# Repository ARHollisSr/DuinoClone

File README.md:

# DuinoClone
Arduino Clone with EEPROM

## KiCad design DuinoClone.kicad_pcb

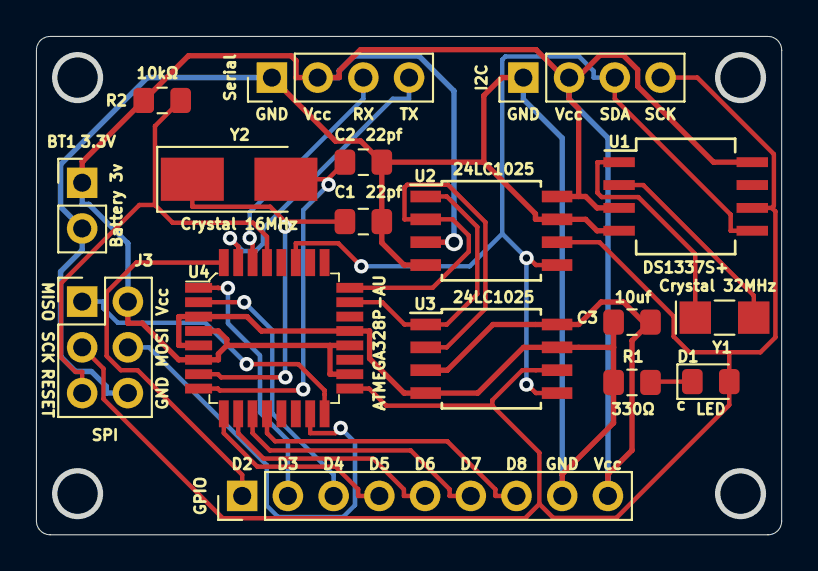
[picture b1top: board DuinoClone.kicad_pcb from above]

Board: 2 copper layers, 41.4 x 27.7 mm, 17 parts (0 on the bottom side), 23 nets.

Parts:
BT1: Battery 3v; PinHeader_1x02_P2.54mm_Vertical
C1, C2: 22pf; C_0805_2012Metric_Pad1.15x1.40mm_HandSolder
C3: 10uf; C_0805_2012Metric_Pad1.15x1.40mm_HandSolder
D1: LED; LED_0805_2012Metric_Pad1.15x1.40mm_HandSolder
GPIO: Digital pins; PinHeader_1x09_P2.54mm_Vertical
I2C: I2C; PinHeader_1x04_P2.54mm_Vertical
J3: SPI; PinHeader_2x03_P2.54mm_Vertical
R1: 330Ω; R_0805_2012Metric_Pad1.15x1.40mm_HandSolder
R2: 10kΩ; R_0805_2012Metric_Pad1.15x1.40mm_HandSolder
Serial: Serial; PinHeader_1x04_P2.54mm_Vertical
U1: DS1337S+; SO-8_5.3x6.2mm_P1.27mm
U2, U3: 24LC1025; SOIJ-8_5.3x5.3mm_P1.27mm
U4: ATMEGA328P-AU; TQFP-32_7x7mm
Y1: Crystal 32MHz; Crystal_SMD_MicroCrystal_CC7V-T1A-2Pin_3.2x1.5mm_HandSolder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
Y2: Crystal 16MHz; Crystal_SMD_5032-2Pin_5.0x3.2mm_HandSoldering

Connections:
/ADDS1: U2.1, U3.1, U4.23
/ADDS2: U2.2, U3.2, U4.24
/D2: GPIO.1, U4.32
/D3: GPIO.2, U4.1
/D4: GPIO.3, U4.2
/D5: GPIO.4, U4.9
/D6: GPIO.5, U4.10
/D7: GPIO.6, U4.11
/D8: GPIO.7, U4.12
/MISO: J3.1, U4.16
/MOSI: J3.4, U4.15
/RESET: J3.5, R2.1, U4.29
/RX: Serial.3, U4.30
/SCK: D1.2, I2C.4, J3.3, U1.6, U2.6, U3.6, U4.17
/SDA: I2C.3, U1.5, U2.5, U3.5, U4.27
/TX: Serial.4, U4.31
/Vcc: BT1.1, C3.1, GPIO.9, I2C.2, J3.2, R2.2, Serial.2, U1.3, U1.8, U2.3, U2.8, U3.3, U3.8, U4.4, U4.6, U4.18, U4.20
GNDPWR: BT1.2, C1.2, C2.2, C3.2, GPIO.8, I2C.1, J3.6, R1.2, Serial.1, U1.4, U2.4, U2.7, U3.4, U3.7, U4.3, U4.5, U4.21
unnamed: C1.1, U4.7, Y2.1
unnamed: C2.1, U4.8, Y2.2
unnamed: D1.1, R1.1
unnamed: U1.1, Y1.1
unnamed: U1.2, Y1.2

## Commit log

2019-05-19 Added parts list
2019-05-19 Created new child schematic sheet, added project symbols
2019-05-19 Added symbol for Atmega328p-au
2019-05-19 Added clock IC custom symbol
2019-05-19 Added crystal symbols to schematic
2019-05-19 Arranged symbols
2019-05-19 Completed associations and added component values
2019-05-19 Finished the hiearchical labels and pins
2019-05-19 Completed wiring connectors sheet
2019-05-19 Completed wiring in root sheet
2019-05-19 Added power flag symbol
2019-05-19 Added functional block descriptions
2019-05-19 Added Netlist
2019-05-20 Created pcbnew
2019-05-20 Set design rules
2019-05-20 First version of pcb component placement
2019-05-20 2nd version pcb component placement
2019-05-20 Created PCB outline and drill holes
2019-05-20 Rerouted board in 2 layers
2019-05-20 Created copper filled area for 2-layer board
2019-05-20 Completed Silk Screen for front copper layer
2019-05-21 Completed Silkscreen work
2019-05-21 Regnerated Gerber files
